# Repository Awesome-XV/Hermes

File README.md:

# Hermes
This is a project that detects motion/object presence. It  uses a TOF distance sensor to detect an object moving or in general. Once the sensor detects it, it sends the signal to the LED to flash. There is also a button that allows for the ability to change units and modes. This makes it work like a motion sensor too, batteries have been included for better mobility and placement of this device.

# Why
I made this project so I can do more complex things in Kicad and have a better understanding on how to use footprints and symbols. This is the first time that I had to go and find them completely on my own. I also added SMD components that will make it cooler. I also added an OLED screen that I can integrate functionality into. Overall, its just a complexity upgrade from my last project so that I can get more into hardware

# Some Pics

# BOM Table
| Name | Purpose | Quantity | Total Cost (USD) | Distributor | Link |
|------|---------|:--------:|-----------------:|-------------|------|
| PCB | Where everything is on top of | 1 | $2.00 | JLCPCB | N/A |
| VL53L1CXV0FY/1 | Proximity Sensor | 1 | $5.77 | Digikey | [Buy](https://www.digikey.com/en/products/detail/stmicroelectronics/VL53L1CXV0FY-1/8258055) |
| CONN HEADER VERT 1POS 2.54MM | Connection from battery pack | 10 | $0.29 | Digikey | [Buy](https://www.digikey.com/en/products/detail/adam-tech/PH1-01-UA/9830231) |
| RES 110 OHM 5% 1/8W AXIAL | Resistor | 10 | $0.22 | Digikey | [Buy](https://www.digikey.com/en/products/detail/stackpole-electronics-inc/CF18JT110R/1741570) |
| DIODE SCHOTTKY 20V 1A DO41 | Prevent reverse flow into batteries | 1 | $0.18 | Digikey | [Buy](https://www.digikey.com/en/products/detail/smc-diode-solutions/1N5817/21705460) |
| XIAO RP2040 | MC | 1 | $4.68 | Digikey | [Buy](https://www.digikey.com/en/products/detail/seeed-technology-co-ltd/102010428/14672129) |
| RES 4.7K OHM 5% 1/8W AXIAL | Resistor | 10 | $0.20 | Digikey | [Buy](https://www.digikey.com/en/products/detail/stackpole-electronics-inc/CF18JT4K70/1741708) |
| CONN HDR 4POS 0.1 GOLD PCB | 4 Pin connector | 1 | $0.38 | Digikey | [Buy](https://www.digikey.com/en/products/detail/sullins-connector-solutions/PPPC041LFBN-RC/810176) |
| CAP CER 0.1UF 50V Z5U RADIAL | Capacitator | 2 | $0.72 | Digikey | [Buy](https://www.digikey.com/en/products/detail/kemet/C315C104M5U5TA/817927) |
| RES 10K OHM 5% 1/4W AXIAL | Resistor | 10 | $0.20 | Digikey | [Buy](https://www.digikey.com/en/products/detail/stackpole-electronics-inc/CF14JT10K0/1741265) |
| BATT HOLDER AA 3 CELL 6" LEADS | Hold Batteries | 1 | $1.76 | Digikey | [Buy](https://www.digikey.com/en/products/detail/keystone-electronics/2465/303814) |
| LED RED DIFFUSED 5MM ROUND T/H | For light | 1 | $0.16 | Digikey | [Buy](https://www.digikey.com/en/products/detail/w%C3%BCrth-elektronik/151051RS11000/4490012) |
| Solder Flux | For my Non-THT components | 1 | $5.99 | Amazon | [Buy](https://www.amazon.com/Solder-Liquid-Soldering-Electrical-Electronics/dp/B0FF793RRY/) |
| PCB Holder | To hold my THT components | 1 | $8.99 | Harbor Freight | N/A |
| D6R90 F2 LFS | Button | 1 | $1.56 | Digikey | [Buy](https://www.digikey.com/en/products/detail/c-k/D6R90-F2-LFS/1466352) |
| Shipping | Move these parts | 1 | $3.12 | JLCPCB, Digikey | N/A |
| Tax | I have to pay | 1 | $4.47 | Digikey | N/A |
| **Total** | | | *$40.69* | | |

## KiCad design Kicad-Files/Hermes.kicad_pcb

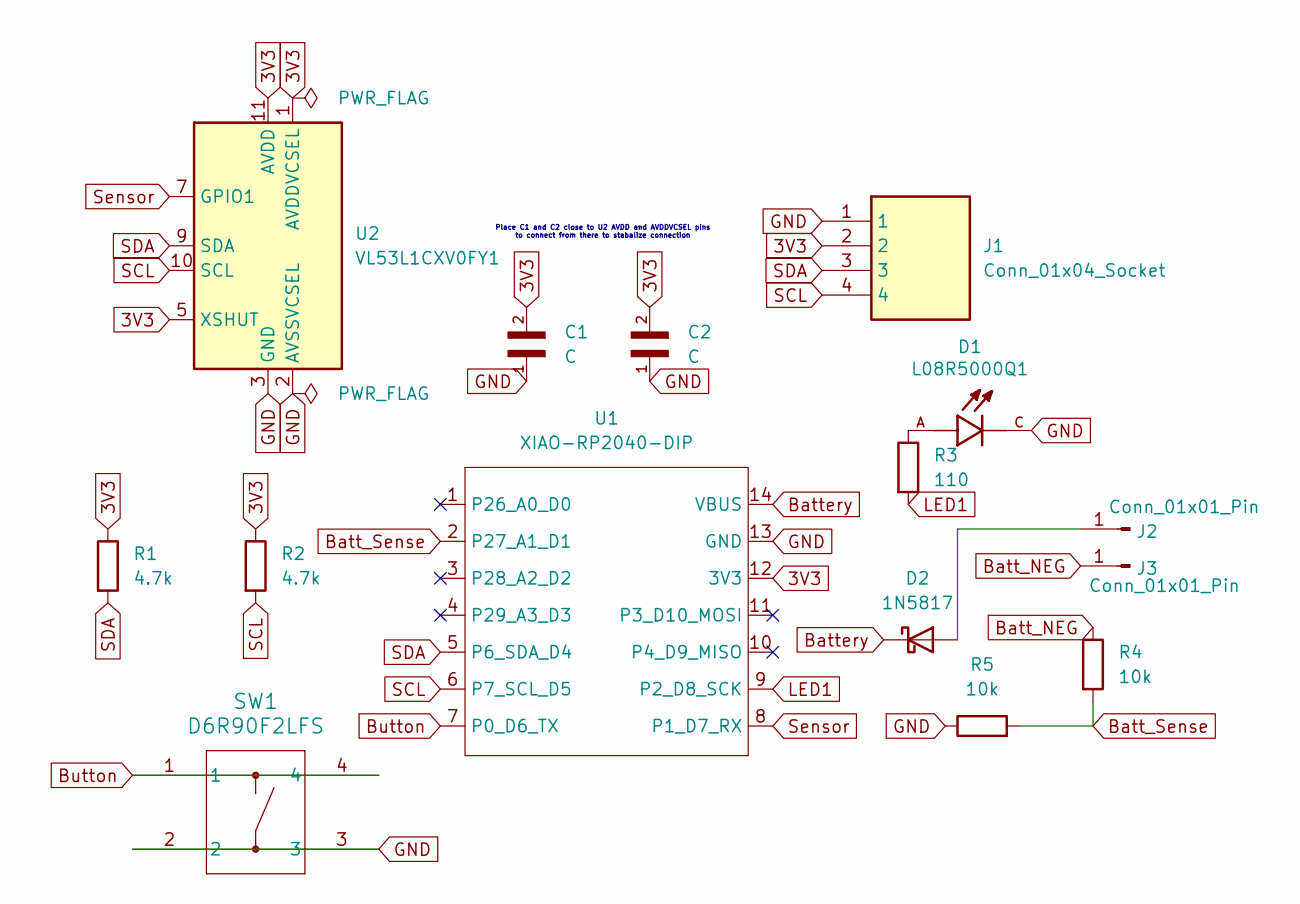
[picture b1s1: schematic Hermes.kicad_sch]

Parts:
C1, C2: C; CAPRR254W54L381T254H466; PARTREV 12/14/2020
D1: L08R5000Q1; LEDRD254W57D500H1070; PARTREV NA
D2: 1N5817; D_DO-41_SOD81_P10.16mm_Horizontal
J1: Conn_01x04_Socket; RHDR4W80P0X254_1X4_1066X254X850P; Manufacturer_Part_Number PPPC041LFBN-RC
J2, J3: Conn_01x01_Pin; PinHeader_1x01_P2.54mm_Vertical
R1, R2: 4.7k; R_Axial_DIN0204_L3.6mm_D1.6mm_P5.08mm_Horizontal
R3: 110; R_Axial_DIN0204_L3.6mm_D1.6mm_P5.08mm_Horizontal
R4, R5: 10k; R_Axial_DIN0207_L6.3mm_D2.5mm_P10.16mm_Horizontal
SW1: D6R90F2LFS; D6R90_CNK
U1: XIAO-RP2040-DIP
U2: VL53L1CXV0FY1; ST_VL53L1x

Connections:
3V3: C1.2, C2.2, J1.2, R1.1, R2.1, U1.12 (3V3), U2.1 (AVDDVCSEL), U2.5 (XSHUT), U2.11 (AVDD)
Batt_NEG: J3.1, R4.1
Batt_Sense: R4.2, R5.2, U1.2 (P27_A1_D1)
Battery: D2.1 (K), U1.14 (VBUS)
Button: SW1.1, SW1.4, U1.7 (P0_D6_TX)
GND: C1.1, C2.1, D1.C, J1.1, R5.1, SW1.2, SW1.3, U1.13 (GND), U2.2 (AVSSVCSEL), U2.3 (GND), U2.4 (GND), U2.6 (GND), U2.12 (GND)
LED1: R3.2, U1.9 (P2_D8_SCK)
unnamed: D1.A, R3.1
unnamed: D2.2 (A), J2.1
SCL: J1.4, R2.2, U1.6 (P7_SCL_D5), U2.10 (SCL)
SDA: J1.3, R1.2, U1.5 (P6_SDA_D4), U2.9 (SDA)
Sensor: U1.8 (P1_D7_RX), U2.7 (GPIO1)

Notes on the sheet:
Place C1 and C2 close to U2 AVDD and AVDDVCSEL pins to connect from there to stabalize connection

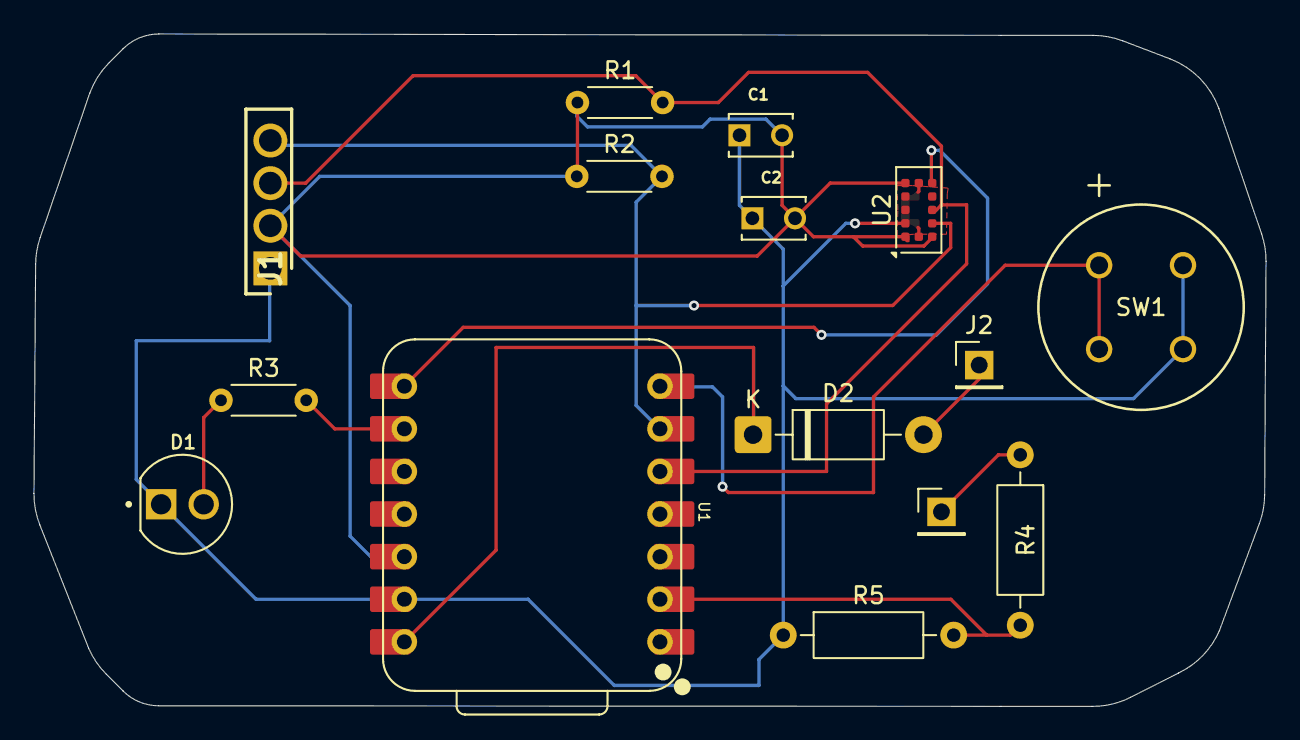
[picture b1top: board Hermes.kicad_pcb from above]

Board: 2 copper layers, 73.4 x 40.1 mm, 15 parts (0 on the bottom side), 12 nets.

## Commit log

2026-04-09 Add PCB and STEP files
2026-04-09 Add some parts of the README
2026-04-09 Organize files and add prod zip file
2026-04-10 Add BOM and update README
2026-04-12 Fix BOM update files and add a button to the pcb
2026-04-12 Add Firmware
2026-04-23 Add CAD source files
2026-04-23 Update README with new project images
    Added additional images to showcase project enhancements.
2026-04-23 Add step file
2026-04-23 Change CAD
